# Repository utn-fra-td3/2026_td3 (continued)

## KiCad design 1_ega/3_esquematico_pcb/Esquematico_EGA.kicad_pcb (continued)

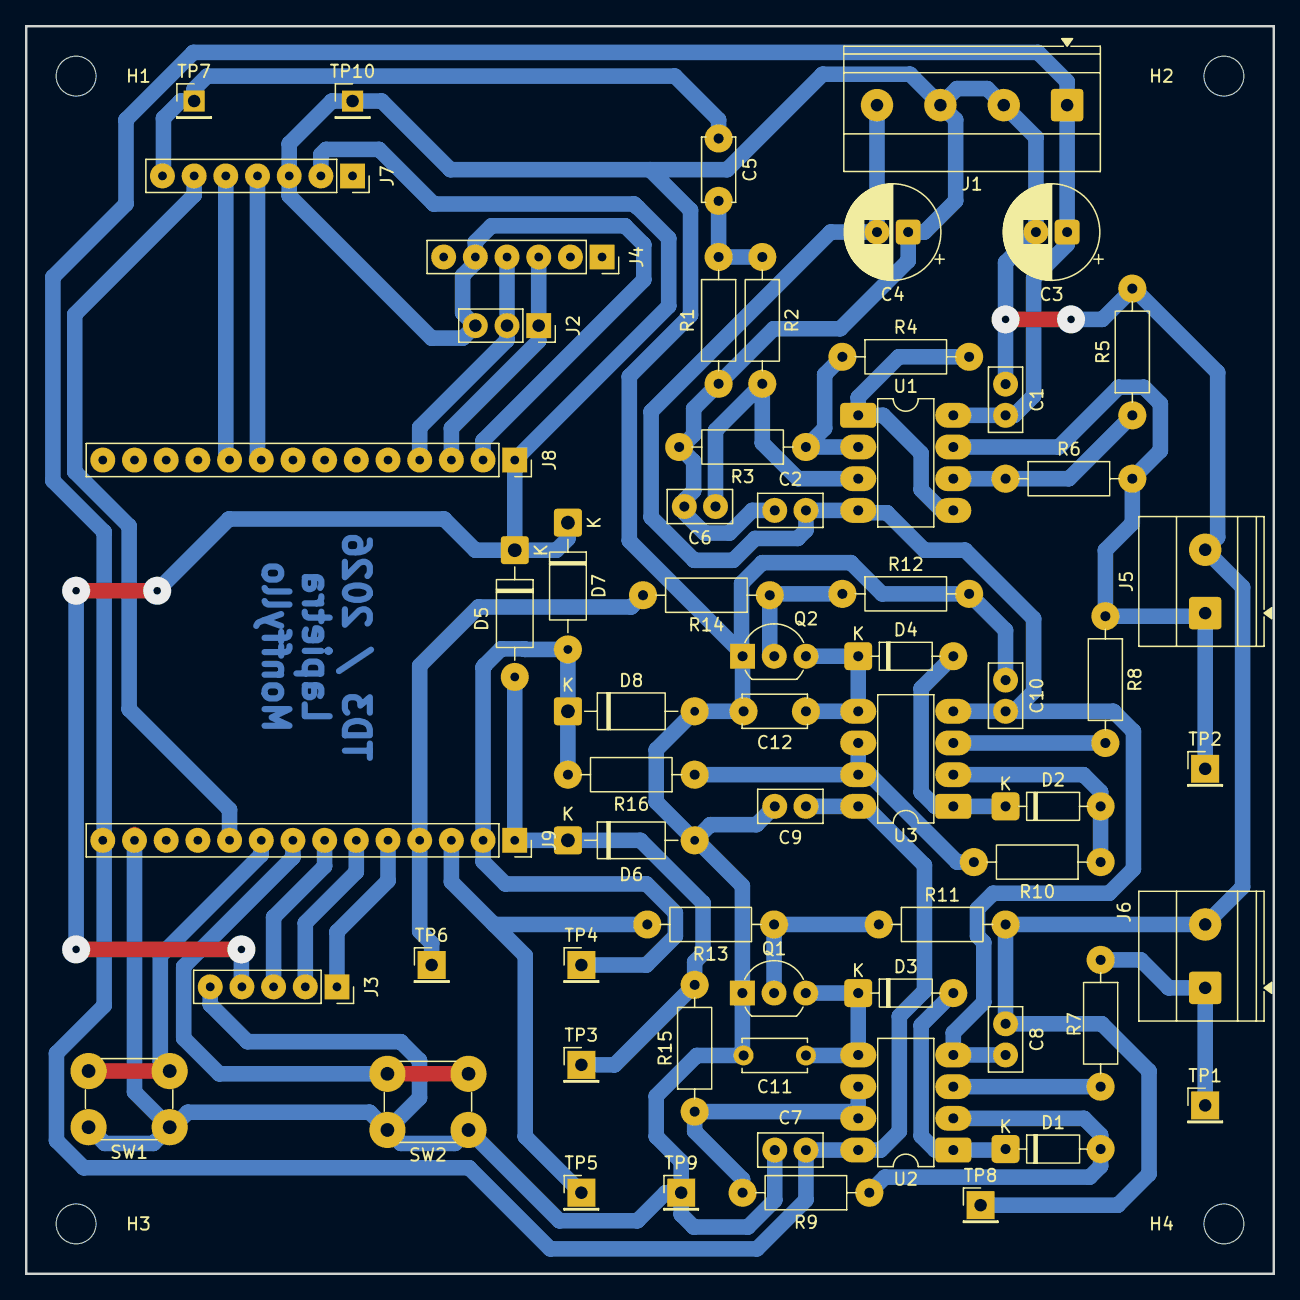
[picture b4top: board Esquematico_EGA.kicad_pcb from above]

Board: 2 copper layers, 100.0 x 100.0 mm, 66 parts (0 on the bottom side), 38 nets.

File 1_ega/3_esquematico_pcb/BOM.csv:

"Reference","Qty","Value","Footprint"
"C1,C2,C7,C8,C9,C10","6","0.1uF","Capacitor_THT:C_Disc_D5.0mm_W2.5mm_P2.50mm"
"C3,C4","2","100uF","Capacitor_THT:CP_Radial_D7.5mm_P2.50mm"
"C5","1","1uF","Capacitor_THT:C_Disc_D5.0mm_W2.5mm_P5.00mm"
"C6","1","150pF","Capacitor_THT:C_Disc_D5.0mm_W2.5mm_P2.50mm"
"C11,C12","2","10uF","Capacitor_THT:C_Disc_D5.0mm_W2.5mm_P5.00mm"
"D1,D2,D3,D4","4","1N4148","Diode_THT:D_DO-35_SOD27_P7.62mm_Horizontal"
"D5,D6,D7,D8","4","1N5819","Diode_THT:D_DO-41_SOD81_P10.16mm_Horizontal"
"J1","1","±5V","TerminalBlock_Phoenix:TerminalBlock_Phoenix_MKDS-1,5-4-5.08_1x04_P5.08mm_Horizontal"
"J2","1","UART","Connector_PinSocket_2.54mm:PinSocket_1x03_P2.54mm_Vertical"
"J3","1","Encoder","Connector_PinSocket_2.54mm:PinSocket_1x05_P2.54mm_Vertical"
"J4","1","CP2102","Connector_PinSocket_2.54mm:PinSocket_1x06_P2.54mm_Vertical"
"J5","1","OUT","TerminalBlock_Phoenix:TerminalBlock_Phoenix_MKDS-1,5-2-5.08_1x02_P5.08mm_Horizontal"
"J6","1","IN","TerminalBlock_Phoenix:TerminalBlock_Phoenix_MKDS-1,5-2-5.08_1x02_P5.08mm_Horizontal"
"J7","1","DDS","Connector_PinSocket_2.54mm:PinSocket_1x07_P2.54mm_Vertical"
"J8,J9","2","Conn_01x14","Connector_PinSocket_2.54mm:PinSocket_1x14_P2.54mm_Vertical"
"Q1,Q2","2","2N7000","Package_TO_SOT_THT:TO-92_Inline_Wide"
"R1","1","100k","Resistor_THT:R_Axial_DIN0207_L6.3mm_D2.5mm_P10.16mm_Horizontal"
"R2,R3,R5,R7,R8,R15,R16","7","1k","Resistor_THT:R_Axial_DIN0207_L6.3mm_D2.5mm_P10.16mm_Horizontal"
"R4","1","2,2k","Resistor_THT:R_Axial_DIN0207_L6.3mm_D2.5mm_P10.16mm_Horizontal"
"R6","1","1,5k","Resistor_THT:R_Axial_DIN0207_L6.3mm_D2.5mm_P10.16mm_Horizontal"
"R9,R10,R11,R12","4","10k","Resistor_THT:R_Axial_DIN0207_L6.3mm_D2.5mm_P10.16mm_Horizontal"
"R13,R14","2","100","Resistor_THT:R_Axial_DIN0207_L6.3mm_D2.5mm_P10.16mm_Horizontal"
"SW1","1","BTN_1","Button_Switch_THT:SW_PUSH_6mm_H5mm"
"SW2","1","BTN_2","Button_Switch_THT:SW_PUSH_6mm_H5mm"
"TP1","1","Vin","Connector_PinHeader_2.54mm:PinHeader_1x01_P2.54mm_Vertical"
"TP2","1","Vout","Connector_PinHeader_2.54mm:PinHeader_1x01_P2.54mm_Vertical"
"TP3","1","Vip","Connector_PinHeader_2.54mm:PinHeader_1x01_P2.54mm_Vertical"
"TP4","1","Vop","Connector_PinHeader_2.54mm:PinHeader_1x01_P2.54mm_Vertical"
"TP5","1","Rst_Vi","Connector_PinHeader_2.54mm:PinHeader_1x01_P2.54mm_Vertical"
"TP6","1","Rst_Vo","Connector_PinHeader_2.54mm:PinHeader_1x01_P2.54mm_Vertical"
"TP7","1","DDS_out","Connector_PinHeader_2.54mm:PinHeader_1x01_P2.54mm_Vertical"
"TP8,TP9,TP10","3","GND","Connector_PinHeader_2.54mm:PinHeader_1x01_P2.54mm_Vertical"
"U1,U2,U3","3","TL072","Package_DIP:DIP-8_W7.62mm_LongPads"

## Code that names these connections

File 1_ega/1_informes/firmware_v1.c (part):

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#define PIN_SPI_CLK      14
#define PIN_SPI_CS       15

#define PIN_ENC_CLK      18
#define PIN_ENC_DT       5
#define PIN_ENC_SW       19   // Botón Encoder: Cambia el PASO de frecuencia
#define PIN_BOTON_MODO   4    // Botón Extra: Cambia la FORMA de onda

#define PIN_I2C_SCL      22
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// UART Configuración (Nativa para Comandos Remotos)
#define UART_PORT_NUM      UART_NUM_0
#define UART_BUF_SIZE      1024
#define PIN_UART_TX        UART_PIN_NO_CHANGE
#define PIN_UART_RX        UART_PIN_NO_CHANGE

// Parámetros DDS
#define SAMPLING_FREQ      25000      
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static void IRAM_ATTR encoder_gpio_isr_handler(void* arg) {
    uint32_t tiempo_actual = esp_timer_get_time();
    if (tiempo_actual - ultimo_tiempo_enc_isr > 35000) { // Debounce 35ms
        int nivel_dt = gpio_get_level(PIN_ENC_DT);
        if (nivel_dt == 1) {
            if (frecuencia_actual + paso_frecuencia <= 20000) frecuencia_actual += paso_frecuencia;
            else frecuencia_actual = 20000;
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        ultimo_modo = ext_btn;

        // --- Monitorear Botón Paso (GPIO 19) ---
        int enc_btn = gpio_get_level(PIN_ENC_SW);
        if (ultimo_sw == 1 && enc_btn == 0) {
            vTaskDelay(pdMS_TO_TICKS(40)); 
            if (gpio_get_level(PIN_ENC_SW) == 0) {
                if (paso_frecuencia == 1)        paso_frecuencia = 10;
                else if (paso_frecuencia == 10)  paso_frecuencia = 100;
                else if (paso_frecuencia == 100) paso_frecuencia = 1000;
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
    // F. Entradas Digitales e Interrupción por hardware del Encoder
    gpio_config_t enc_cfg = { 
        .pin_bit_mask = (1ULL << PIN_ENC_CLK) | (1ULL << PIN_ENC_DT), 
        .mode = GPIO_MODE_INPUT, 
        .pull_up_en = GPIO_PULLUP_ENABLE, 
        .pull_down_en = GPIO_PULLDOWN_DISABLE, 
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    ESP_ERROR_CHECK(gpio_config(&enc_cfg)); 

    gpio_config_t botones_cfg = { 
        .pin_bit_mask = (1ULL << PIN_ENC_SW) | (1ULL << PIN_BOTON_MODO), 
        .mode = GPIO_MODE_INPUT, 
        .pull_up_en = GPIO_PULLUP_ENABLE, 
        .pull_down_en = GPIO_PULLDOWN_DISABLE, 
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    if (err_isr != ESP_OK && err_isr != ESP_ERR_INVALID_STATE) {
        ESP_LOGE(TAG, "Fallo al inicializar servicio ISR");
    }
    ESP_ERROR_CHECK(gpio_isr_handler_add(PIN_ENC_CLK, encoder_gpio_isr_handler, NULL));

    // G. Inicializar Conductor UART0
    uart_config_t uart_config = {
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    };
    ESP_ERROR_CHECK(uart_driver_install(UART_PORT_NUM, UART_BUF_SIZE * 2, 0, 0, NULL, 0));
    ESP_ERROR_CHECK(uart_param_config(UART_PORT_NUM, &uart_config));
    ESP_ERROR_CHECK(uart_set_pin(UART_PORT_NUM, PIN_UART_TX, PIN_UART_RX, UART_PIN_NO_CHANGE, UART_PIN_NO_CHANGE));

    // H. Inicializar Conductor I2C Maestro para OLED (v6.0)
    i2c_master_bus_config_t i2c_bus_config = { .clk_source = I2C_CLK_SRC_DEFAULT, .i2c_port = I2C_NUM_0, .scl_io_num = PIN_I2C_SCL, .sda_io_num = PIN_I2C_SDA, .glitch_ignore_cnt = 7, .flags.enable_internal_pullup = true };
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
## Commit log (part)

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2025-07-03 perf: soporte para custom FreeRTOSConfig desde aplicacion y mejora de definicion de rutas de acuerdo a arquitectura
2025-07-03 feat: soporte para picow
2025-07-03 chore: elimino tarea de inicializacion
2025-07-03 chore: detalle estetico del CMakeLists
2025-07-03 chore: elimino tarea de init
2025-07-03 chore: elimino tarea init
2025-07-03 chore: detalle estetico en inclusion de archivo
2025-07-03 chore: elimino tarea de init y doy soporte a picow
2025-07-03 chore: instruccion mas generica
2025-07-03 chore: mejoro inclusion de freertos
2025-07-03 feat: ejemplo de software timers
2025-07-03 docs: instrucciones sobre biblioteca de freertos
2025-07-03 docs: documentacion sobre cada definicion de freertos
2025-07-03 perf: habilita eleccion de heap
2025-07-03 chore: aclaración sobre personalización de freertos
2025-07-03 docs: actualización de referencias a manuales de FreeRTOS
2025-07-04 feat: ejemplo de static blinky
2025-07-04 perf: flexibilizacion sobre el uso de configuracion de usuario
2025-07-04 docs: documentacion de uso de configuracion de usuario
2025-07-04 chore: elimino contenido erroneo sobre inclusion de freertos
2025-07-04 chore: instruccion de cmake como en la documentacion
2025-07-04 chore: instrucciones de cmake actualizadas a las de la documentacion
2025-07-04 chore: readme de los proyectos
2025-07-04 feat: ejemplo de software timer estatico
2025-07-04 docs: manual de freertos de richard barry
2025-07-04 docs: ejemplos linkeados y ordenados por unidades
2025-07-04 feat: ejemplo de static queue
2025-07-04 chore: arreglo del titulo
2025-07-04 chore: agrego referencia a ejemplo
2025-07-16 feat: ejemplos de gpos
2025-07-16 docs: listado de ejemplos
2025-07-18 feat: soporte para abstraccion de hardware para el GPIO
2025-07-18 chore: ignoro directorio de build
2025-07-18 docs: consigna de TP5
2025-07-18 chore: makefile de guia
2025-07-18 chore: template de guia
2025-07-19 chore: setup basico
2025-09-15 docs: apuntes de clase de unidad 3
2025-09-15 docs: bibliografia unidad 3
2025-09-15 chore: readmes de unidades tematicas
2025-09-15 docs: apuntes de clase de unidad 4
2025-09-15 docs: bibliografia de linux embebido
2025-09-22 docs: presentacion de intro a linux
2025-10-24 chore: directorio y contenido de egb
2026-03-18 docs: libro linux embebido
2026-03-18 docs: apunte gpos
2026-06-01 Agrego Diagram en Bloques
2026-06-01 docs: diagrama de tareas y de bloques
2026-06-01 docs: diagramas de tareas y de bloques
2026-06-01 Adjunto diagrama en bloques
2026-06-01 Adicion de diagramas de tareas y de bloques v1
2026-06-01 Adicion diagramas
2026-06-01 primer entrega EGA
2026-06-02 Entrega Diagrama en bloques y de tareas
2026-06-02 Entrega1
2026-06-02 fix diagrama de tareas
2026-06-02 Primer entrega EGA1
2026-06-03 Subiendo diagramas
2026-06-03 agrego diagrama de tareas
2026-06-03 agrego diagrama en bloques
2026-06-03 Se agrega mapa de tareas y esquema
2026-06-03 agrego diagrama de tareas y bloques
2026-06-03 Se agregan diagramas .png
2026-06-03 Se borran archivos .pdf
2026-06-03 agrego diagrama de tareas (corregido) y bloques
2026-06-03 Entrega de mapa de tareas y diagrama en bloques
2026-06-03 diagrama de bloques
2026-06-03 diagrama en bloques
2026-06-03 Subiendo los diagramas
2026-06-03 diagrama de tareas
2026-06-03 Revert "Merge branch 'utn-fra-td3:main' into ega/v1"
    This reverts commit 921fad73fec5d0f6647a61cc478a1ee40666025a, reversing
    changes made to 96e932683d5ec393eb53ed42fafc01d03bc4ec54.
2026-06-03 Entrega de mapa de tareas corregido
2026-06-03 Primer entrega EGA
    Entrega de diagrama de conexion y diagrama de tareas de carga electronica
2026-06-04 docs: add task diagram
2026-06-04 docs: add conection diagram
2026-06-04 agregar ega.pdf
2026-06-04 Agregar .gitignore del workspace
2026-06-04 Agregar referencias del AD9833 y ESP32-S3
2026-06-04 Eliminar carpeta freertos del workspace
2026-06-04 Se actualizo diagrama en bloques y se agrego diagrama de tareas.
2026-06-04 estructura inicial del proyecto
2026-06-05 Se actualiza el diagrama en bloques y se carga el diagrama de tareas
2026-06-05 chore: agregar archivos 1_informes
2026-06-05 chore: agregar pcb kicad
2026-06-05 chore: agregar informes ega
2026-06-05 chore: agregar pcb inicio
2026-06-06 display funcionando con LVGL
2026-06-06 flash size 16MB
2026-06-06 integrar UI generada por SquareLine Studio
2026-06-06 touch CST816S funcionando
2026-06-07 agregar fuente RobotoMono 14px con caracteres en español
2026-06-08 correccion de diagramas.
2026-06-08 Diagramas ADC integrado y datasheets
2026-06-08 ADC con lectura one shoot
2026-06-08 adicion de interrupciones y tarea interfaz.
2026-06-08 entrega informe preliminar
2026-06-08 Adjunto Preliminar
2026-06-08 add informe preliminar
2026-06-08 vuelvo a subir lo mismo pero en formato png
2026-06-08 vuelvo a subir lo mismo en formato png
2026-06-09 redirigir console a USB Serial/JTAG para separar logs de UART0
2026-06-09 chore:se agrega informe preliminar ega
2026-06-09 implementar recepción de comandos UART por línea
2026-06-10 Subiendo informe preliminar
2026-06-10 Agrego proyecto SquareLine
2026-06-10 Entrega de informe preliminar
2026-06-11 agrego preinforme
2026-06-11 pre informe Generador de señales. Gutierrez-Caceres
2026-06-11 Se sube preliminar
2026-06-11 Agrego informe Preliminar
2026-06-11 Informe Preliminar
2026-06-11 Entrega informe EGA
2026-06-15 Informe final
2026-06-15 Informe IEEE
2026-06-15 Creacion de tareas y codigo.
2026-06-16 esquematico y pcb
2026-06-16 simulaciones LTSpice
2026-06-16 borrar archivos temporales
2026-06-16 actualizar diagrama en bloques
2026-06-16 agrego task_sweep adc uart nvs task_menu
2026-06-17 añadir referencias esp32-s3 y opamp
2026-06-17 agregar imagenes de simulacion
2026-06-17 driver CP2102 para windows
2026-06-17 ad9833 funcionando para generar senoidales
2026-06-17 agregar inicializacion de NVS en task_nvs
2026-06-17 Subiendo codigo actual
2026-06-17 feat(runoff) : agrego interrución y tarea ONN/OFF
2026-06-17 Se sube firmware, PCB y esquematico
2026-06-17 Segunda entrega firmware pcb y esquematico
2026-06-17 subo codigo
2026-06-17 docs(pcb): se agrega esquemático
2026-06-17 entrega 2
2026-06-17 docs: agrego informe preliminar
2026-06-18 feat: consigna ega
2026-06-18 commit nuevo
2026-06-18 Tareas guardianas, Caceres-Gutierrez
2026-06-18 encoder controlando pwm con tarea guardiana
2026-06-18 Estructura de codigo para informe final
2026-06-19 feat: add mcp4725 test
2026-06-19 actualizar esquemático y layout PCB
2026-06-21 armar pantallas de config y barrido
2026-06-21 agregar teclado numerico
2026-06-21 agregar queue_menu_events y queue_display
2026-06-21 conectar config de pantalla y UART a menu_config con validacion
2026-06-21 actualización PCB y esquemático
2026-06-21 actualizar diagrama de tareas
2026-06-22 code: agrego tareas encoder, oled y eeprom
2026-06-22 Mejora de código, integración de tareas.
2026-06-23 Agrego informe final.
2026-06-23 Actualizo Informe Final.pdf con estructura del firmware
2026-06-23 Docs: informe
    Se carga version actualizada del informe
2026-06-23 Docs: informe
    se carga version actualizada de informe
2026-06-23 Fix: diagrama en bloques
    se agrega sck en ADC y se cambia SCK por BCK
2026-06-23 Fix: diagrama de bloques
    se agrega SCK en ADC y se cambia SCK por BCK
2026-06-23 feat: workspace ecualizador
    se añade el workspace del proyecto
2026-06-23 fix: workspace
    se sube la carpeta correcta, versión equivocada en feat anterior
2026-06-23 Corrección de repositorio.
2026-06-23 Corrección de repositorio.
2026-06-23 Subiendo PCB y esquematico
2026-06-24 task_uart como tarea guardiana del puerto UART
2026-06-24 corregir decimales de kHz y unidad de asentamiento en lcd_display
2026-06-24 validar configuracion de conjunto al iniciar barrido y mostrar popup de error, UART solo RX comandos / TX datos de medicion
2026-06-24 chore: ignorar backup y cache de SquareLine Studio
2026-06-24 feat: implementar medicion del barrido en task_sweep
2026-06-24 Actualizando codigo
2026-06-24 Actualizando diagrama en bloques
2026-06-24 Subiendo informe final
2026-06-24 feat: graficar el barrido en pantalla y enviar puntos por UART
2026-06-24 actualizar diagrama para tener tarea guardiana de UART
2026-06-24 Cambiar operacional por el TL072
2026-06-24 Actualizando PCB, esquematico e informe
2026-06-24 actualizaciones y PCB
2026-06-24 docs(informe): agrego informe ega
2026-06-25 Se sube informe final
2026-06-25 actualizar informe
2026-06-27 feat(flash): agrego componente flash
2026-06-27 feat(lcd): agrego componente lcd
2026-06-27 feat(teclado): agrego componente teclado
2026-06-28 fix: evitar log10(0) en la medicion y fijar escala dB para el grafico
2026-06-28 fix: mejora visual de decimales en esala de frecuencia y ampliar limite de tiempo de asentamiento
2026-06-28 feat: componentes y display tft
2026-06-28 feat: maquina de estados en menu_config
2026-06-28 feat: implementar task_user_controls para botones fisicos BTN1/BTN2
2026-06-29 feat: agregar mensajes de error para el usuario
2026-06-29 fix: error en cola
2026-06-29 actualizar Proyecto SquareLine Studio
2026-06-29 fix Diagrama de Tareas
    Se reemplaza el diagrama de tareas ajustado al main final
2026-06-29 Fix: diagrama de tareas
    se reemplaza diagrama de tareas ajustado a app main final
2026-06-29 Fix Informe
    Se carga la ultima revision del informe
2026-06-29 Fix: informe
    se carga la última revisión del informe
2026-06-29 docs Resolucion Cuestionario
    Se añade la resolucion del cuestionario
2026-06-29 Docs: cuestionario
    se añade la resolucion del cuestionario
2026-06-29 feat main
    Se sube ultima version funcional del main
2026-06-29 Feat: main
    se sube ultima version funcional del main
2026-06-29 docs esquema y pcb
    Se añade el circuito esquematico y el diseño de pcb
2026-06-29 Docs: esquematico y pcb
    se añaden esquematico y pcb del circuito
2026-06-29 Docs: anexos
    se adjuntan anexos como video funcionando, fotos y manual de usuario
2026-06-29 docs anexos
    Se añaden los anexos correspondientes. Renders 3d, Video Funcionando, Ensamble Final, y manual de usuario
2026-06-29 feat: guardar y cargar configuracion del barrido en NVS
2026-06-29 feat: implementar comandos start pause y cancel en UART
2026-06-29 fix: no enviar valores repetidos por uart
2026-06-29 docs: agrego proyecto kicad
2026-06-29 Entrega final.
2026-06-29 Corrección.
2026-06-30 entrega EGA1
2026-06-30 refactor: manejar debounce de botones con reset de queue_btn_isr en vez de gpio_intr_disable/enable
2026-06-30 feat: prioridad de lvgl igual que lcd_display en forma explicita
2026-06-30 fix: encender backlight despues de armar la UI
2026-06-30 docs: actualizar diagrama de tareas
2026-06-30 docs: actualizar valores de componentes
2026-06-30 actualizar valores de componentes
